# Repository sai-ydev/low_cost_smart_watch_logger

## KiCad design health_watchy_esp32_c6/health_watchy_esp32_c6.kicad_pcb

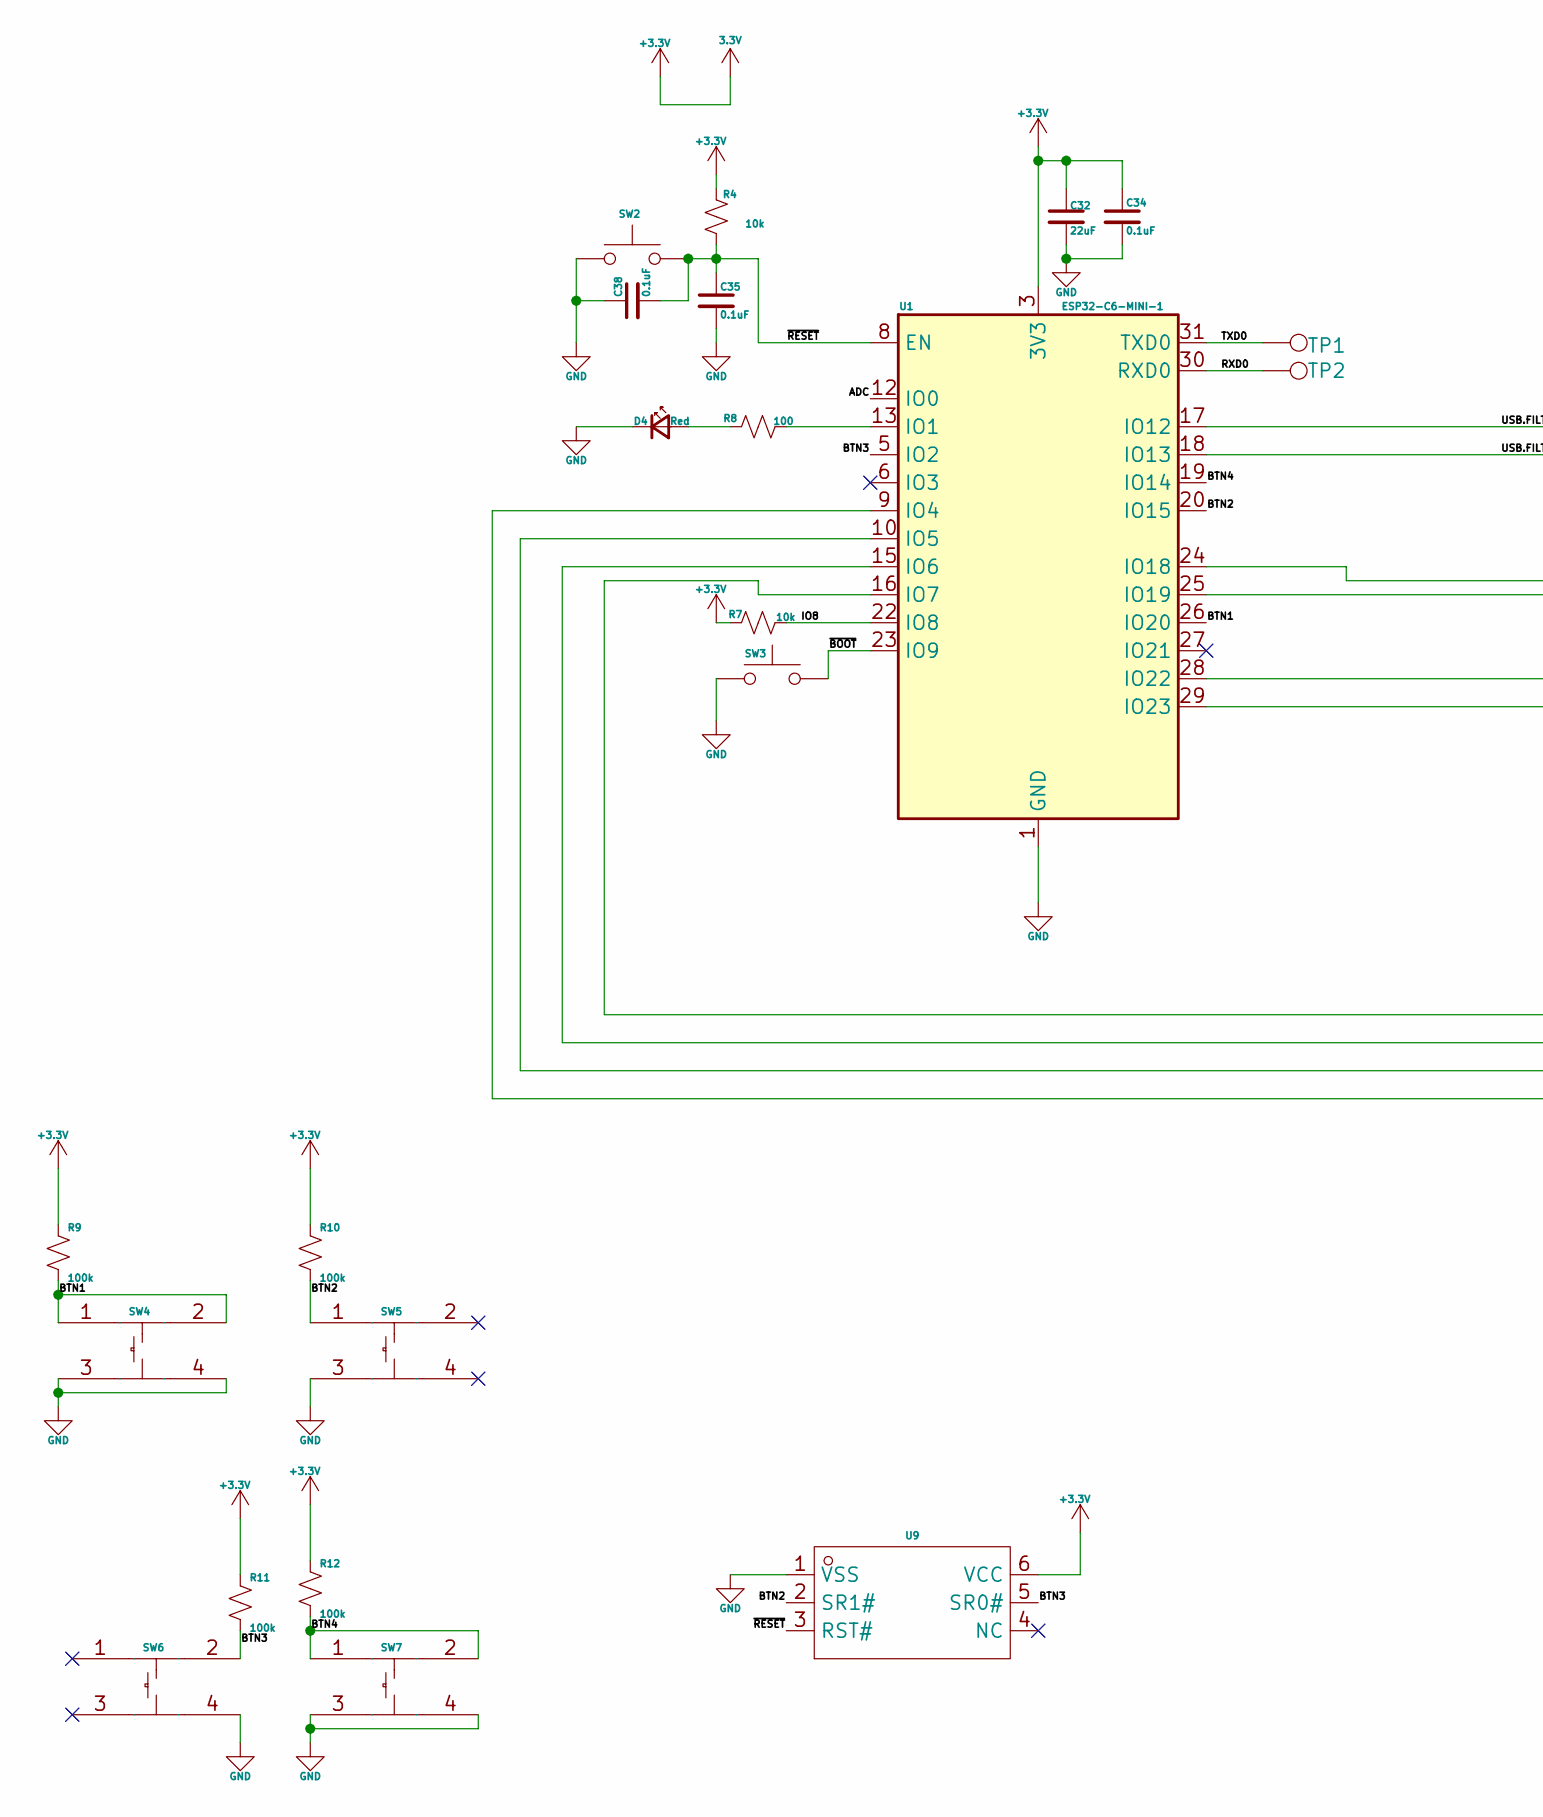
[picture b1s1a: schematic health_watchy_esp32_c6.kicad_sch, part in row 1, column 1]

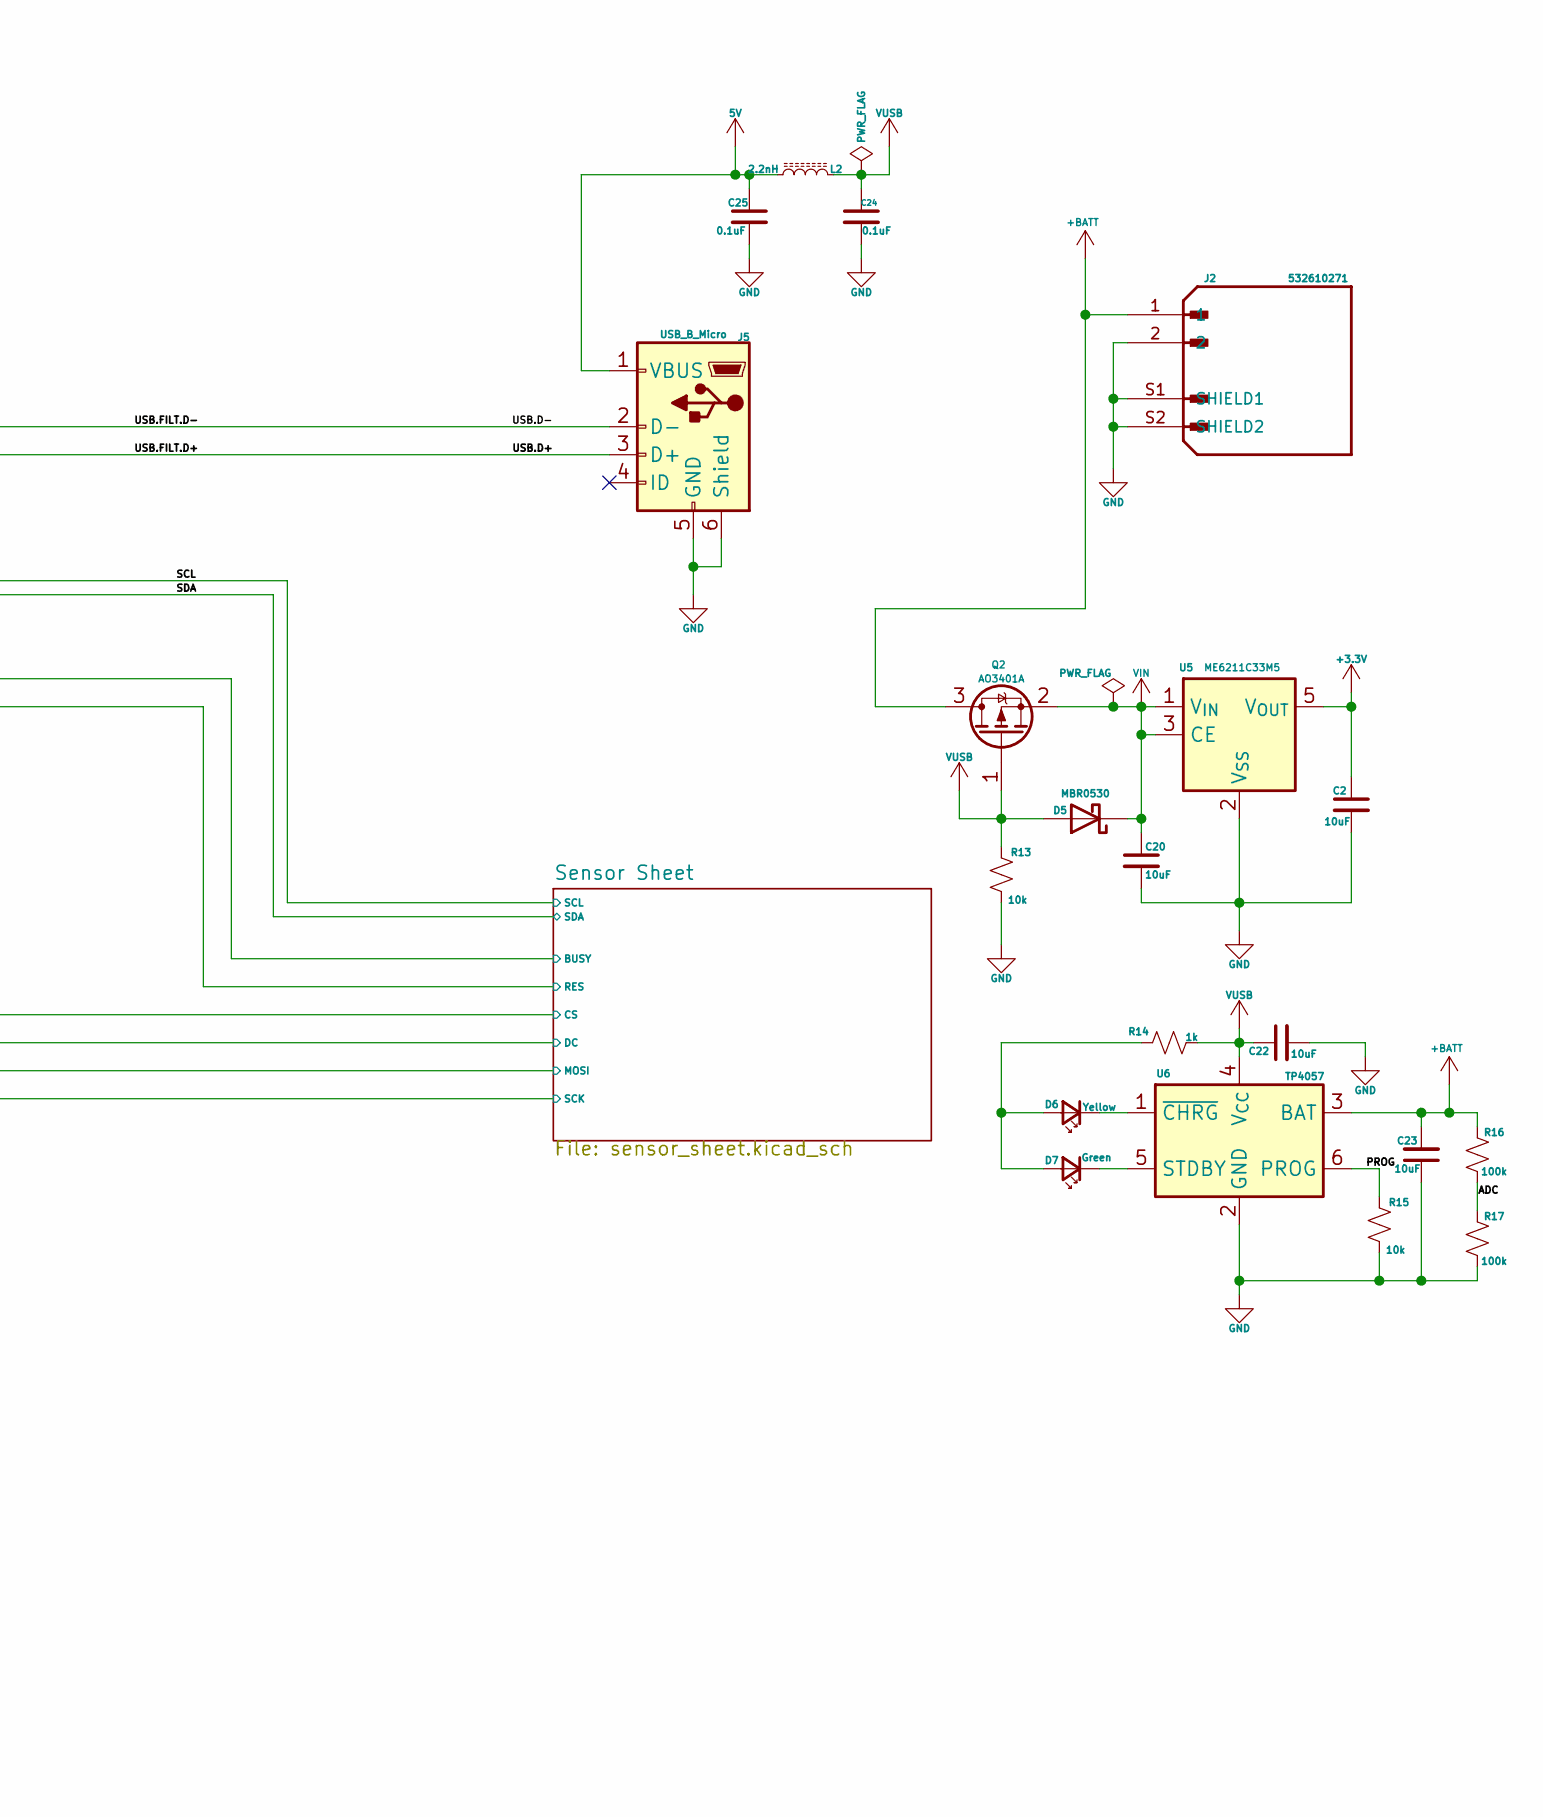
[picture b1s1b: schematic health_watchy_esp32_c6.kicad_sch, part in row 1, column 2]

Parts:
C2, C20, C22, C23: 10uF; C_0402_1005Metric; Voltage 6.3V; Tolerance 20%
C24, C25: 0.1uF; C_0402_1005Metric; Voltage 6.3V; Tolerance 10%
C32: 22uF; C_0402_1005Metric; Voltage 10V; Tolerance 10%
C34, C35, C38: 0.1uF; C_0402_1005Metric; Voltage 16V; Tolerance 10%
D4: Red; LED_0402_1005Metric_Red
D5: MBR0530; SOD-523
D6: Yellow; LED_0402_1005Metric
D7: Green; LED_0402_1005Metric
J2: 532610271; MOLEX_532610271; PARTREV J; DigiKey_Part_Number WM7620CT-ND
J5: USB_B_Micro; USB_Micro-B_Amphenol_10103594-0001LF_Horizontal
L2: 2.2nH; L_0402_1005Metric
Q2: AO3401A; SOT-23
R4, R7, R13, R15: 10k; R_0402_1005Metric
R8: 100; R_0402_1005Metric
R9, R10, R11, R12, R16, R17: 100k; R_0402_1005Metric
R14: 1k; R_0402_1005Metric
SW2, SW3: SMD_4.6x2.8mm_h2.5mm; Push_SMD_4.6x2.8mm_h2.5mm
SW4, SW5, SW6, SW7: KEY-SMD_4P-L4.8-W4.6-P1.70-LS6.2; Manufacturer Part K2-1114SA-A4SW-06; LCSC Part Name 4.8mm*3.5mm*1.65mm 12V 50mA
TP1, TP2: 0.5mm; TestPoint-0.5mm
U1: ESP32-C6-MINI-1
U5: ME6211C33M5; SOT-23-5
U6: TP4057; TSOT-23-6
U9: UDFN-6_L1.6-W1.3-P0.40-TL; Manufacturer Part SR2HARU; LCSC Part Name 6引脚智能复位设备

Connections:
5V: C25.1, J5.1 (VBUS), L2.2
+3.3V: C2.1, C32.1, C34.1, R4.2, R7.2, R9.2, R10.2, R11.2, R12.2, U1.3 (3V3), U5.5 (V_{OUT}), U9.6 (VCC); also elsewhere on the board
+BATT: C23.2, J2.1, Q2.3 (D), R16.2, U6.3 (BAT)
/ADC: R16.1, R17.2, U1.12 (IO0)
/BTN1: R9.1, SW4.1, SW4.2, U1.26 (IO20)
/BTN2: R10.1, SW5.1, U1.20 (IO15), U9.2 (SR1#)
/BTN3: R11.1, SW6.2, U1.5 (IO2), U9.5 (SR0#)
/BTN4: R12.1, SW7.1, SW7.2, U1.19 (IO14)
/IO8: R7.1, U1.22 (IO8)
/PROG: R15.2, U6.6 (PROG)
/RXD0: TP2.1, U1.30 (RXD0)
/SCL: U1.24 (IO18); also elsewhere on the board
/SDA: U1.25 (IO19); also elsewhere on the board
/Sensor Sheet/BUSY: U1.28 (IO22); also elsewhere on the board
/Sensor Sheet/CS: U1.16 (IO7); also elsewhere on the board
/Sensor Sheet/DC: U1.15 (IO6); also elsewhere on the board
/Sensor Sheet/MOSI: U1.10 (IO5); also elsewhere on the board
/Sensor Sheet/RES: U1.29 (IO23); also elsewhere on the board
/Sensor Sheet/SCK: U1.9 (IO4); also elsewhere on the board
/TXD0: TP1.1, U1.31 (TXD0)
/USB.D+: J5.3 (D+), U1.18 (IO13)
/USB.D-: J5.2 (D-), U1.17 (IO12)
/~BOOT: SW3.2, U1.23 (IO9)
/~RESET: C35.1, C38.2, R4.1, SW2.2, U1.8 (EN), U9.3 (RST#)
GND: C2.2, C20.2, C22.2, C23.1, C24.2, C25.2, C32.2, C34.2, C35.2, C38.1, D4.1 (K), J2.2, J2.S1 (SHIELD1), J2.S2 (SHIELD2), J5.5 (GND), J5.6 (Shield), R13.1, R15.1, R17.1, SW2.1, SW3.1, SW4.3, SW4.4, SW5.3, SW6.4, SW7.3, SW7.4, U1.1 (GND), U1.2 (GND), U1.11 (GND), U1.14 (GND), U1.36 (GND), U1.37 (GND), U1.38 (GND), U1.39 (GND), U1.40 (GND), U1.41 (GND), U1.42 (GND), U1.43 (GND), U1.44 (GND), U1.45 (GND), U1.46 (GND), U1.47 (GND), U1.48 (GND), U1.49 (GND), U1.50 (GND), U1.51 (GND), U1.52 (GND), U1.53 (GND), U5.2 (V_{SS}), U6.2 (GND), U9.1 (VSS); also elsewhere on the board
unnamed: D4.2 (A), R8.1
unnamed: D6.2 (A), D7.2 (A), R14.1
unnamed: D6.1 (K), U6.1 (~CHRG)
unnamed: D7.1 (K), U6.5 (STDBY)
unnamed: R8.2, U1.13 (IO1)
VIN: C20.1, D5.1 (K), Q2.2 (S), U5.1 (V_{IN}), U5.3 (CE)
VUSB: C22.1, C24.1, D5.2 (A), L2.1, Q2.1 (G), R13.2, R14.2, U6.4 (V_{CC})

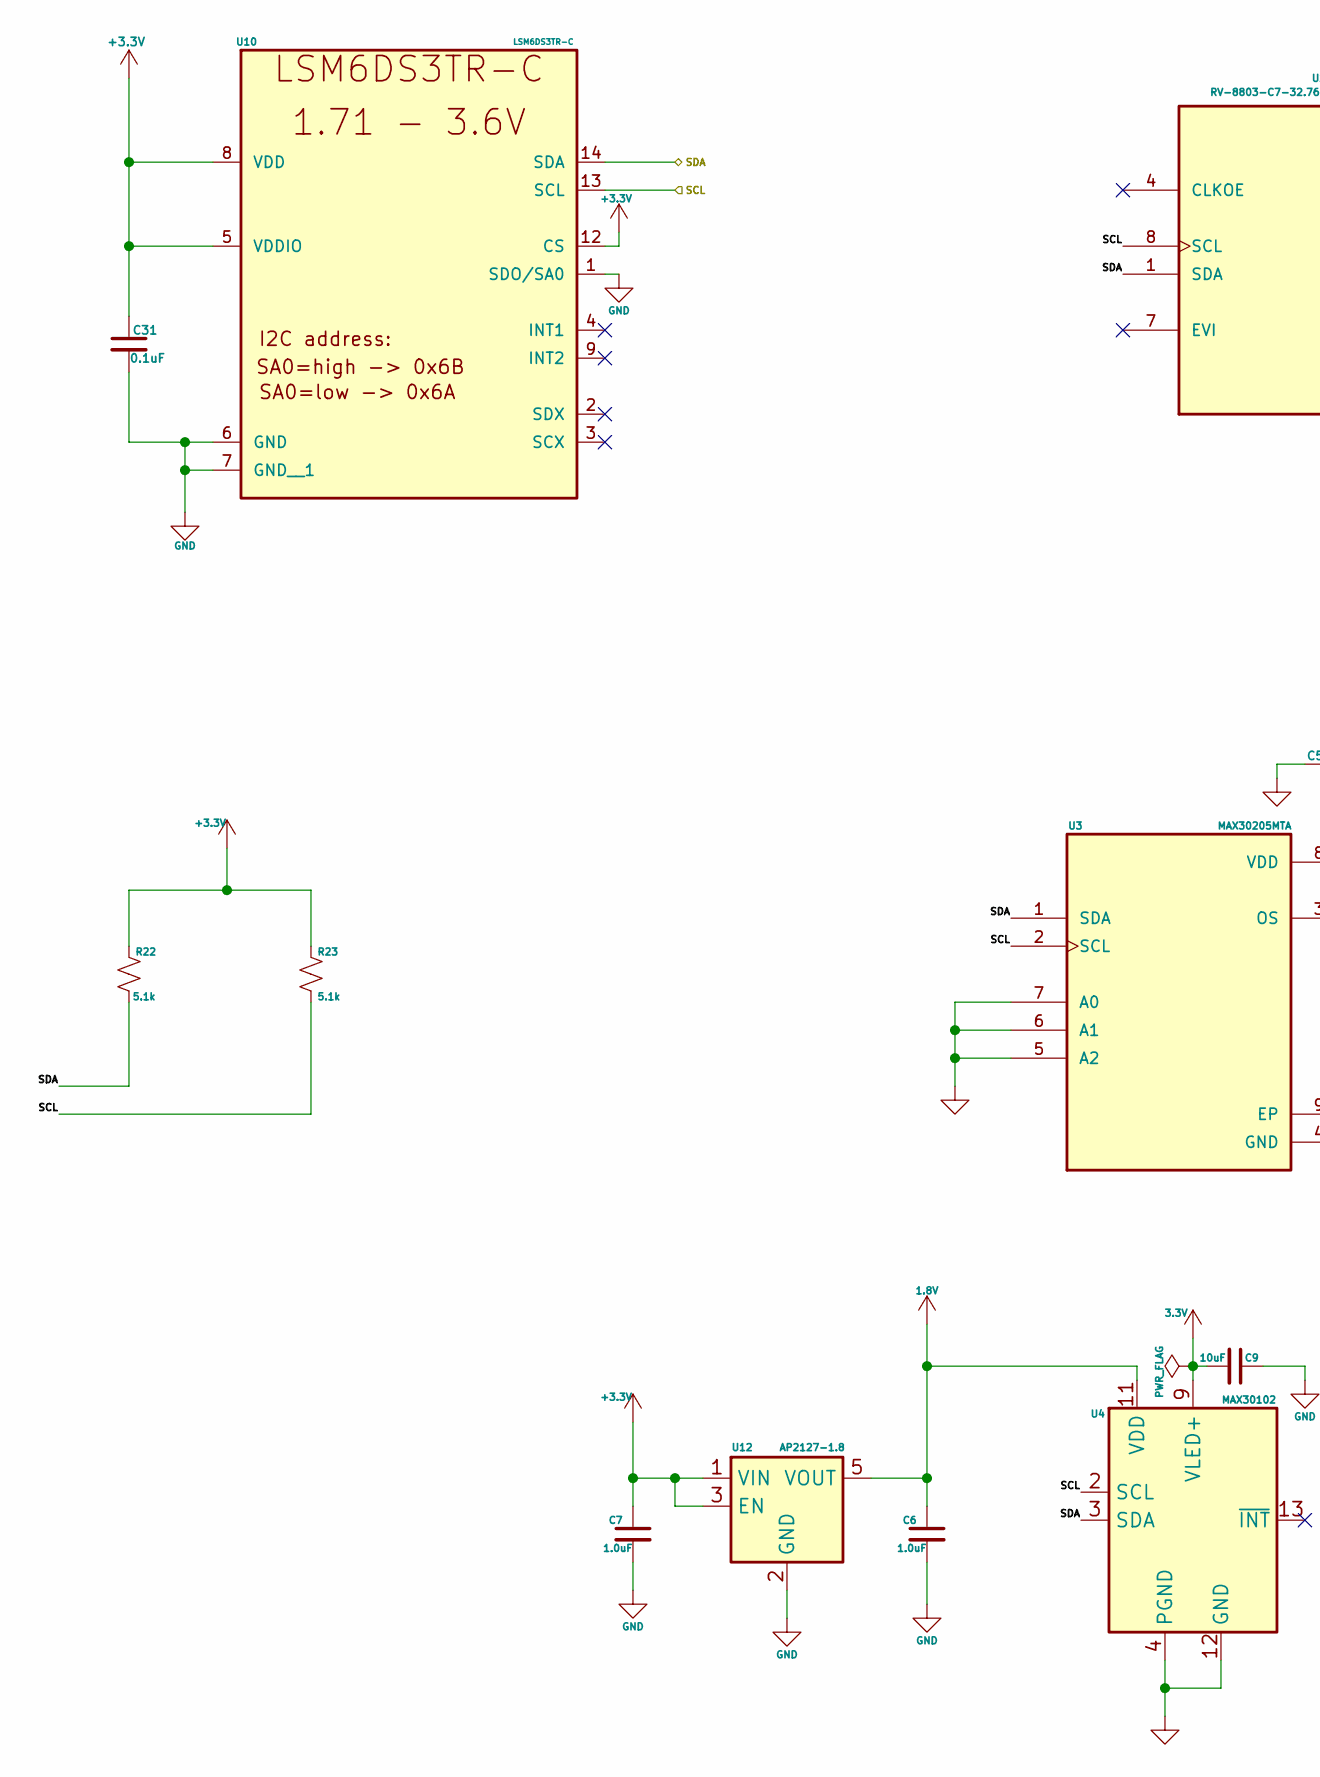
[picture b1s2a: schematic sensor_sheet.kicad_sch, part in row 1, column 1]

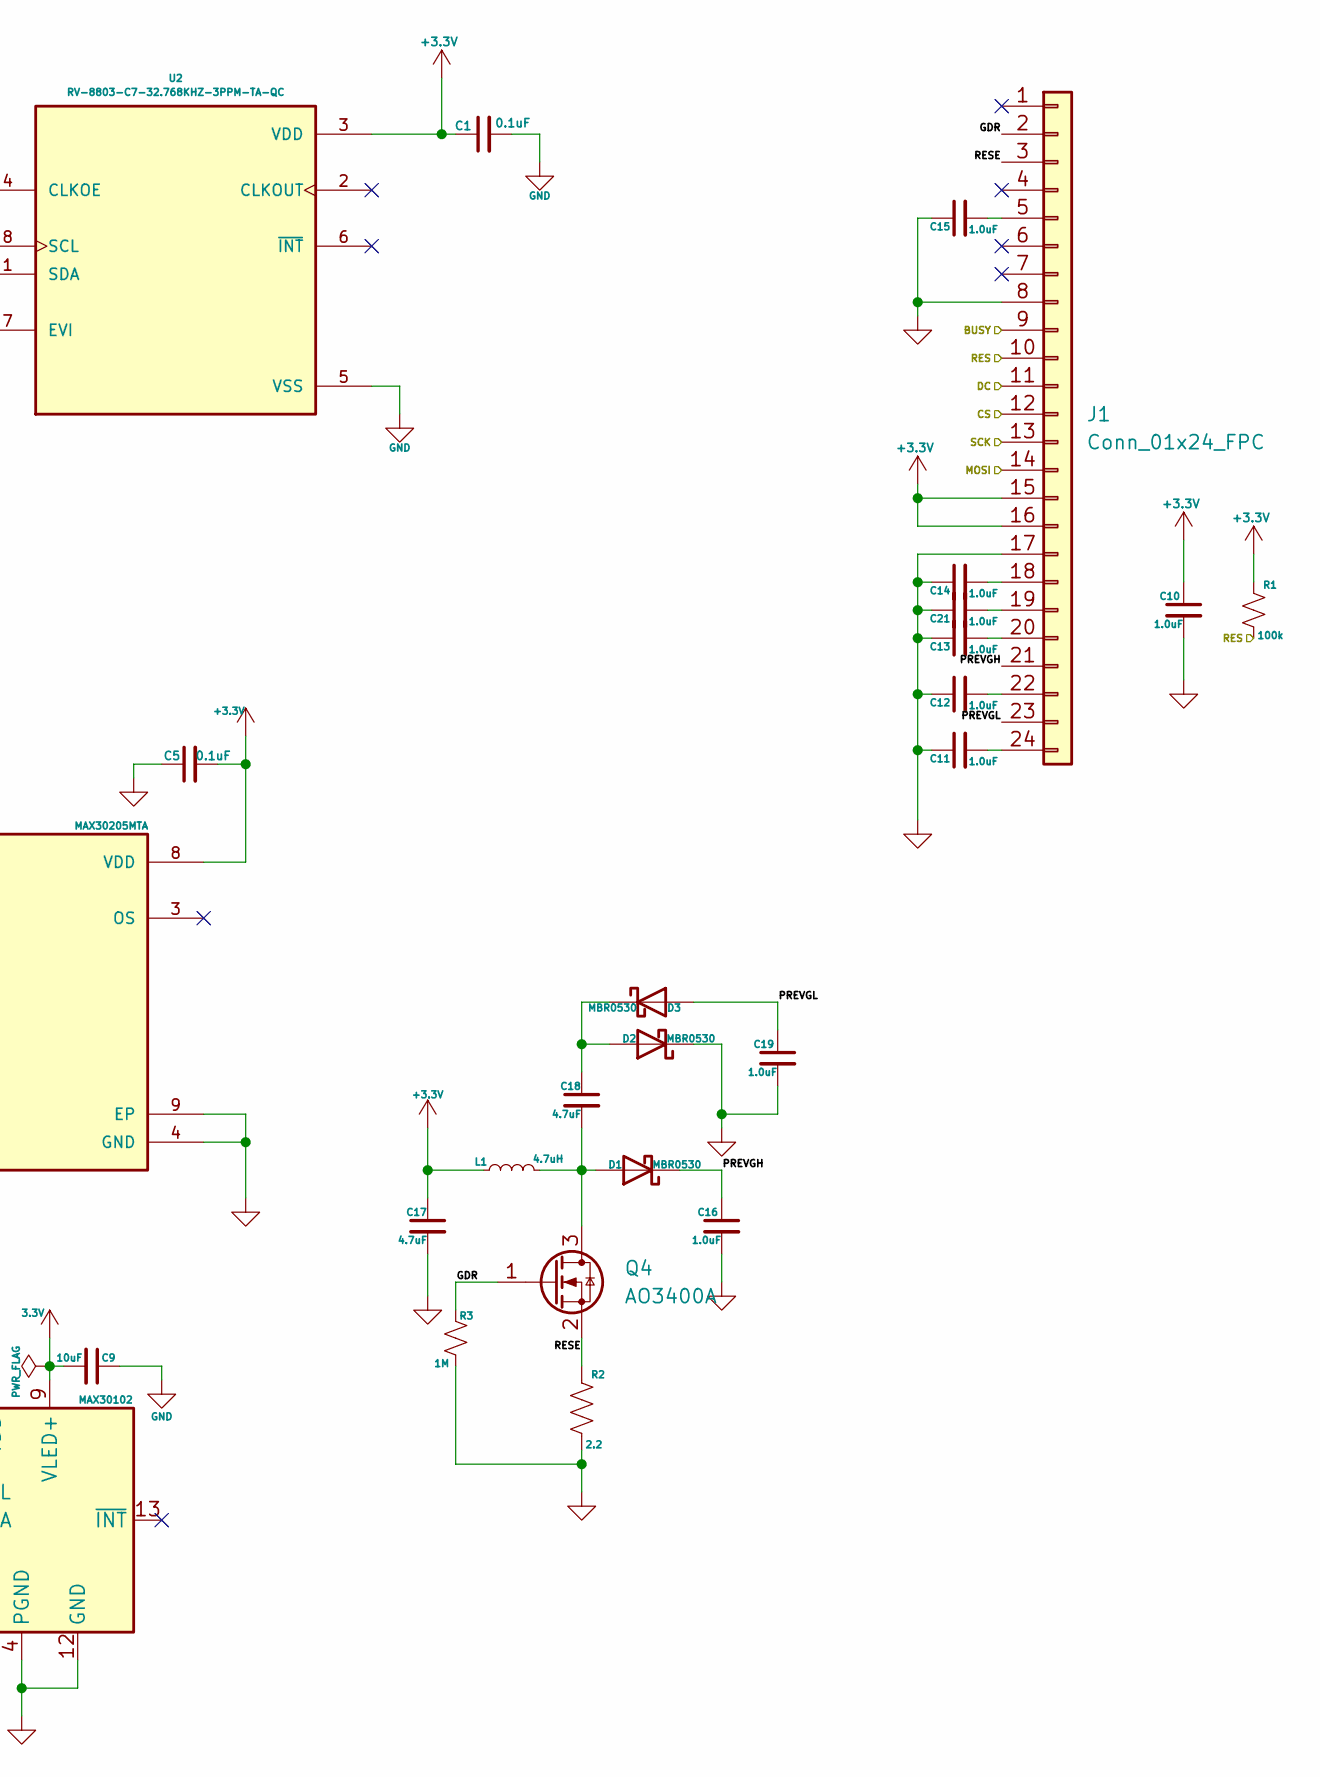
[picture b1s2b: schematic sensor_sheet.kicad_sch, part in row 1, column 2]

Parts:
C1, C5, C31: 0.1uF; C_0402_1005Metric; Voltage 16V; Tolerance 10%; LCSC C60474
C6, C7: 1.0uF; C_0402_1005Metric; Voltage 16V; Tolerance 10%
C9: 10uF; C_0402_1005Metric; Voltage 6.3V; Tolerance 20%
C10, C11, C12, C13, C14, C15, C16, C19, C21: 1.0uF; C_0402_1005Metric; Voltage 50V; Tolerance 10%
C17, C18: 4.7uF; C_0402_1005Metric; Voltage 6.3V; Tolerance 20%
D1, D2, D3: MBR0530; D_SOD-523
J1: Conn_01x24_FPC; FPC_1x24_P0.5mm_Horizontal_BottomContact
L1: 4.7uH; L_0402_1005Metric
Q4: AO3400A; SOT-23
R1: 100k; R_0402_1005Metric
R2: 2.2; R_0402_1005Metric
R3: 1M; R_0402_1005Metric
R22, R23: 5.1k; R_0402_1005Metric
U2: RV-8803-C7-32.768KHZ-3PPM-TA-QC; IC_RV-8803-C7-32.768KHZ-3PPM-TA-QC; PARTREV 5.1/06.2018
U3: MAX30205MTA; SON65P300X300X80-9N
U4: MAX30102; Maxim_OLGA-14_3.3x5.6mm_P0.8mm
U10: LSM6DS3TR-C; LGA-14-2.5X3MM
U12: AP2127-1.8; SOT23-5

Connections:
1.8V: C6.1, U4.11 (VDD), U12.5 (VOUT)
+3.3V: C1.1, C5.2, C7.1, C9.2, C10.1, C17.1, C31.1, J1.15, J1.16, L1.1, R1.2, R22.2, R23.2, U2.3 (VDD), U3.8 (VDD), U4.9 (VLED+), U4.10 (VLED+), U10.5 (VDDIO), U10.8 (VDD), U10.12 (CS), U12.1 (VIN), U12.3 (EN); also elsewhere on the board
/SCL: R23.1, U2.8 (SCL), U3.2 (SCL), U4.2 (SCL), U10.13 (SCL); also elsewhere on the board
/SDA: R22.1, U2.1 (SDA), U3.1 (SDA), U4.3 (SDA), U10.14 (SDA); also elsewhere on the board
/Sensor Sheet/BUSY: J1.9; also elsewhere on the board
/Sensor Sheet/CS: J1.12; also elsewhere on the board
/Sensor Sheet/DC: J1.11; also elsewhere on the board
/Sensor Sheet/GDR: J1.2, Q4.1 (G), R3.2
/Sensor Sheet/MOSI: J1.14; also elsewhere on the board
/Sensor Sheet/PREVGH: C16.1, D1.1 (K), J1.21
/Sensor Sheet/PREVGL: C19.1, D3.2 (A), J1.23
/Sensor Sheet/RES: J1.10, R1.1; also elsewhere on the board
/Sensor Sheet/RESE: J1.3, Q4.2 (S), R2.1
/Sensor Sheet/SCK: J1.13; also elsewhere on the board
GND: C1.2, C5.1, C6.2, C7.2, C9.1, C10.2, C11.1, C12.1, C13.1, C14.1, C15.1, C16.2, C17.2, C19.2, C21.1, C31.2, D2.1 (K), J1.8, J1.17, R2.2, R3.1, U2.5 (VSS), U3.4 (GND), U3.5 (A2), U3.6 (A1), U3.7 (A0), U3.9 (EP), U4.4 (PGND), U4.12 (GND), U10.1 (SDO/SA0), U10.6 (GND), U10.7 (GND__1), U12.2 (GND); also elsewhere on the board
unnamed: C18.2, D1.2 (A), L1.2, Q4.3 (D)
unnamed: C18.1, D2.2 (A), D3.1 (K)
unnamed: C15.2, J1.5
unnamed: C14.2, J1.18
unnamed: C21.2, J1.19
unnamed: C13.2, J1.20
unnamed: C12.2, J1.22
unnamed: C11.2, J1.24

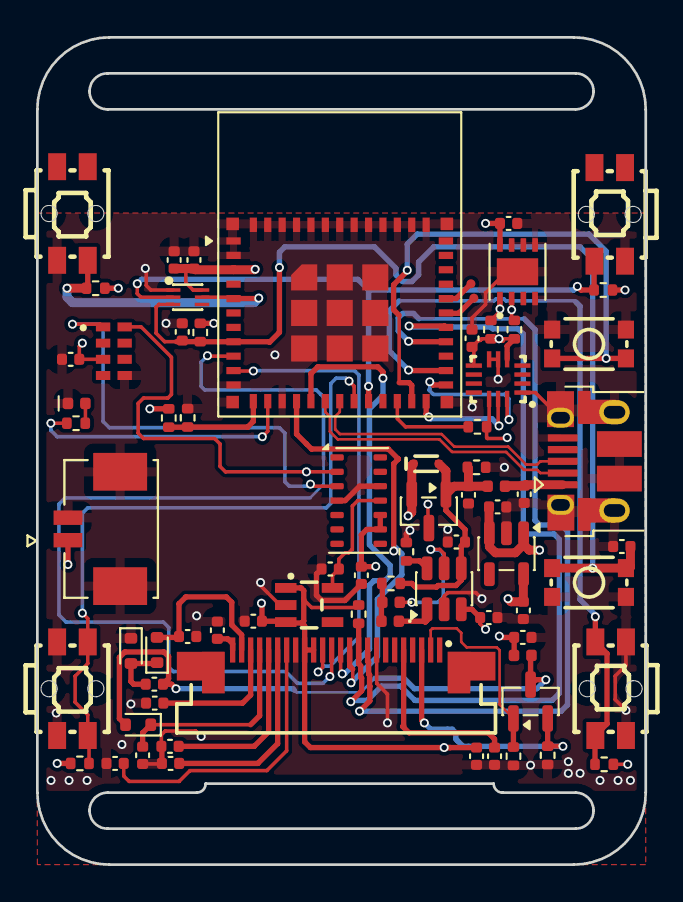
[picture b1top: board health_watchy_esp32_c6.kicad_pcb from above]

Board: 4 copper layers, 33.8 x 46.0 mm, 75 parts (0 on the bottom side), 45 nets.

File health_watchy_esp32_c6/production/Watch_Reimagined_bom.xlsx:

Designator | Footprint | Quantity | Value | LCSC Part #
C1, C31, C5, C24, C25, C34, C35, C38 | 0402 | 8 | 0.1uF | C1581
C10, C11, C12, C13, C14, C15, C16, C19, C21, C6, C7 | 0402 | 11 | 1.0uF | C1518208
C17, C18 | 0402 | 2 | 4.7uF | C23733
C2, C20, C22, C23, C9 | 0402 | 5 | 10uF | C15525
C32 | 0402 | 1 | 22uF | C105226
D1, D2, D3, D5 | SOD-523 | 4 | MBR0530 | C8522
D4 | 0402 | 1 | Red | C71911
D6 | 0402 | 1 | Yellow | C71911
D7 | 0402 | 1 | Green | C74338
J1 | FPC_1x24_P0.5mm_Horizontal_BottomContact | 1 | Conn_01x24_FPC | C3169639
J2 | MOLEX_532610271 | 1 | 532610271 | C177225
J5 | USB_Micro-B_Amphenol_10103594-0001LF_Horizontal | 1 | USB_B_Micro | C428495
L1 | 0402 | 1 | 4.7uH | C7261423
L2 | 0402 | 1 | 2.2nH | C27122
Q2 | SOT-23 | 1 | AO3401A | C15127
Q4 | SOT-23 | 1 | AO3400A | C344010
R1, R10, R11, R12, R16, R17, R9 | 0402 | 7 | 100k | C25530
R13, R15, R4, R7 | 0402 | 4 | 10k | C25744
R14 | 0402 | 1 | 1k | C11702
R2 | 0402 | 1 | 2.2000000000000002 | C269402
R22, R23 | 0402 | 2 | 5.1k | C25905
R3 | 0402 | 1 | 1M | C26083
R8 | 0402 | 1 | 100 | C82865
SW2, SW3 | Push_SMD_4.6x2.8mm_h2.5mm | 2 | SMD_4.6x2.8mm_h2.5mm | C72443
SW4, SW5, SW6, SW7 | KEY-SMD_4P-L4.8-W4.6-P1.70-LS6.2 | 4 | ~ | C136662
TP1, TP2 | TestPoint-0.5mm | 2 | 0.5mm | DNP
U1 | ESP32-C6-MINI-1 | 1 | ESP32-C6-MINI-1 | C5736265
U10 | LGA-14-2.5X3MM | 1 | LSM6DS3TR-C | C967633
U12 | SOT23-5 | 1 | AP2127-1.8 | C151375
U2 | IC_RV-8803-C7-32.768KHZ-3PPM-TA-QC | 1 | RV-8803-C7-32.768KHZ-3PPM-TA-QC | C2846926
U3 | SON65P300X300X80-9N | 1 | MAX30205MTA | C476171
U4 | Maxim_OLGA-14_3.3x5.6mm_P0.8mm | 1 | MAX30102 | C6454833
U5 | SOT-23-5 | 1 | ME6211C33M5 | C82942
U6 | TSOT-23-6 | 1 | TP4057 | C12044
U9 | UDFN-6_L1.6-W1.3-P0.40-TL | 1 | ~ | SR2HARU

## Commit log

2026-01-23 Power schematic
2026-02-02 Design files update
2026-02-03 Checking in library
2026-02-11 Checking in completed design files.
2026-03-05 Design files
